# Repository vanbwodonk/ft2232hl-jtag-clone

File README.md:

# FT2232HL-jtag-clone

Digilent JTAG clone hardware + eeprom firmware (.bin). Support dual port, JTAG + Serial TTL. Hardware design using KiCad. 

## Pinout FT2232HL

JTAG:

| Pin FT2232HL | JTAG Name | FT2232 Name |
|:------------:|:---------:|:-----------:|
| 16           | TCK       | ADBUS0      |
| 17           | TDI       | ADBUS1      |
| 18           | TDO       | ADBUS2      |
| 19           | TMS       | ADBUS3      |

Serial UART:

| Pin FT2232HL | JTAG Name | FT2232 Name |
|:------------:|:---------:|:-----------:|
| 38           | TXD       | BDBUS0      |
| 39           | RXD       | BDBUS1      |

### How To Flash EEPROM

[how-to-flash](https://github.com/vanbwodonk/ft2232hl-jtag-clone/blob/main/eeprom_binary/README.md)

### Source :

Thanks to @rikka0w0 for provide binary files modification .Source : https://gist.github.com/rikka0w0/24b58b54473227502fa0334bbe75c3c1

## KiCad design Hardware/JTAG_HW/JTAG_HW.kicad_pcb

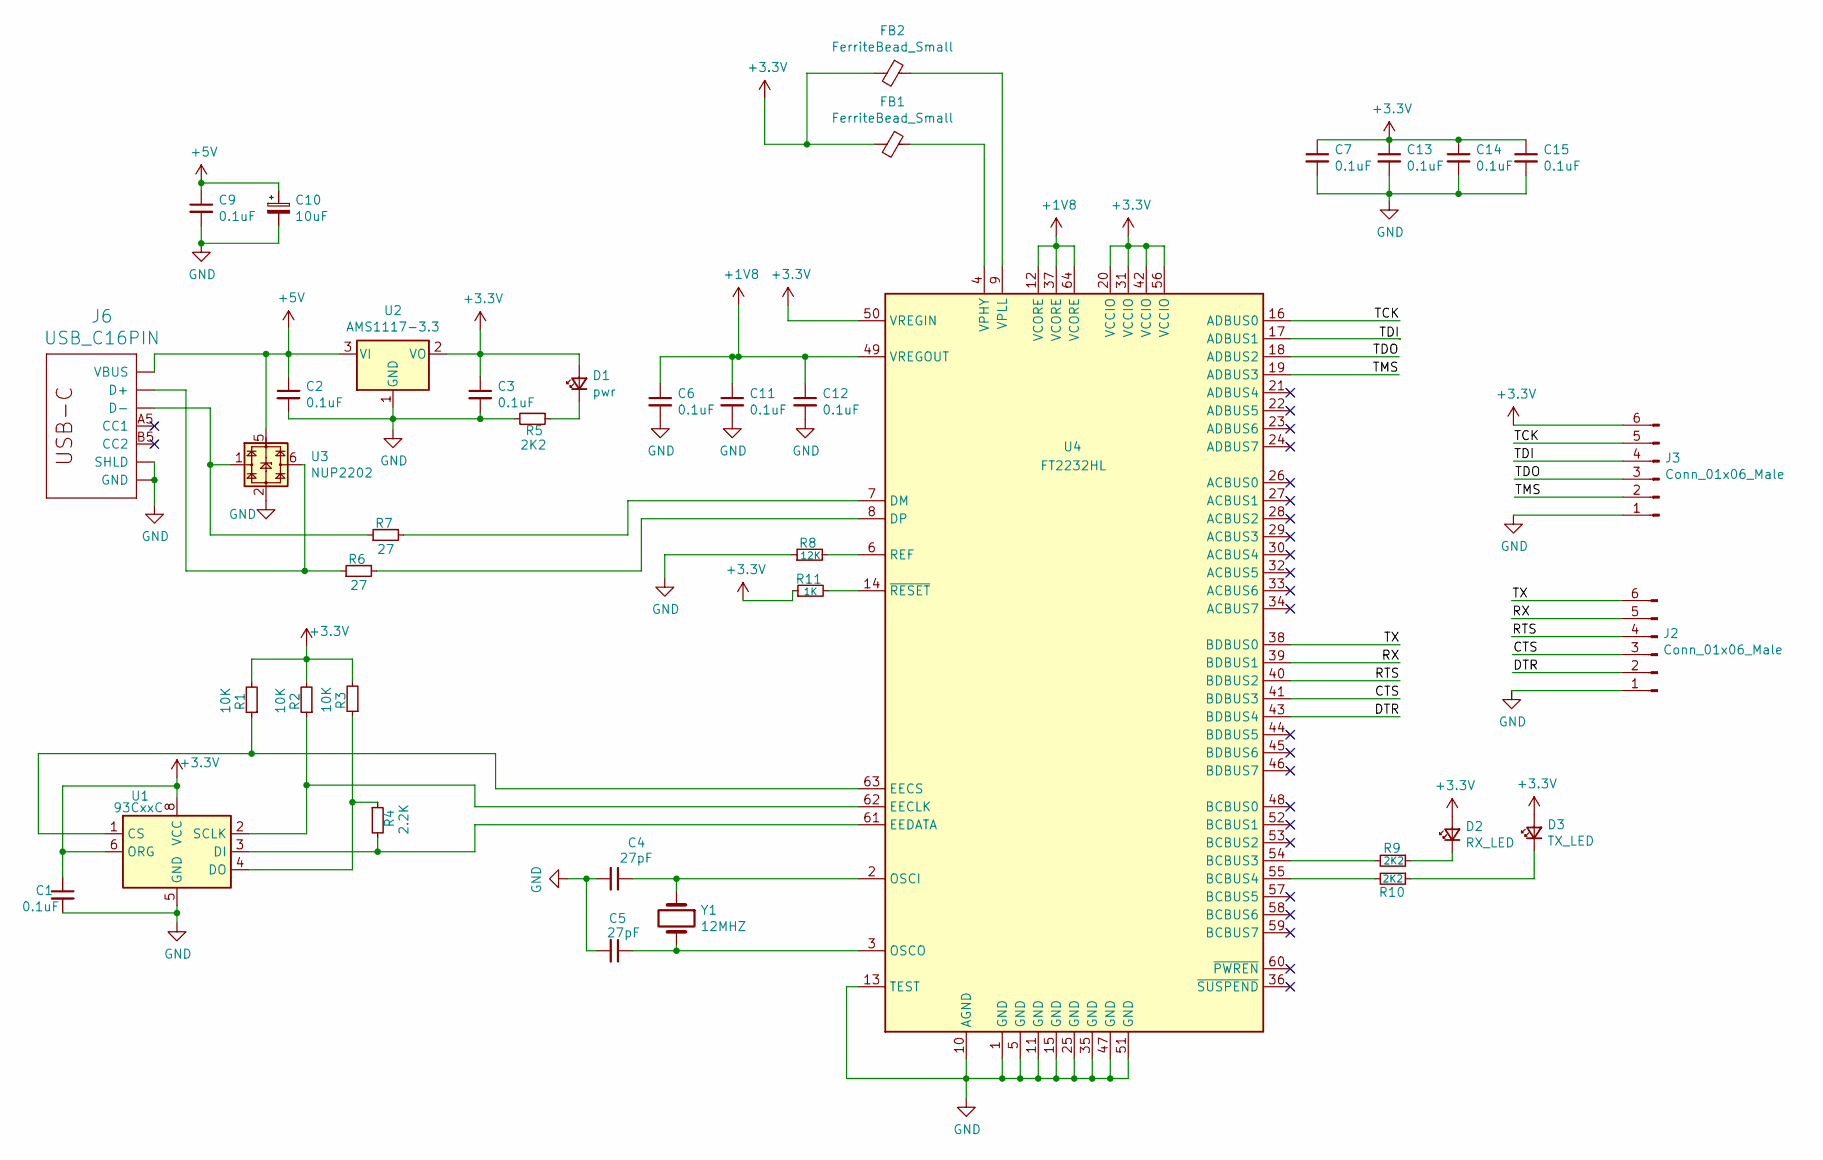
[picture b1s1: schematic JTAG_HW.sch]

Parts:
C1, C2, C3, C6, C7, C9, C11, C12, C13, C14, C15: 0.1uF; C_0805_2012Metric_Pad1.18x1.45mm_HandSolder
C4, C5: 27pF; C_0805_2012Metric_Pad1.18x1.45mm_HandSolder
C10: 10uF; CP_EIA-3216-18_Kemet-A_Pad1.58x1.35mm_HandSolder
D1: pwr; LED_0805_2012Metric_Pad1.15x1.40mm_HandSolder
D2: RX_LED; LED_0805_2012Metric_Pad1.15x1.40mm_HandSolder
D3: TX_LED; LED_0805_2012Metric_Pad1.15x1.40mm_HandSolder
FB1, FB2: FerriteBead_Small; L_0805_2012Metric_Pad1.15x1.40mm_HandSolder
J2, J3: Conn_01x06_Male; PinHeader_1x06_P2.54mm_Vertical_SMD_Pin1long
J6: USB_C16PIN; USB-C-COM-15111
R1, R2, R3: 10K; R_0805_2012Metric_Pad1.20x1.40mm_HandSolder
R4: 2.2K; R_0805_2012Metric_Pad1.20x1.40mm_HandSolder
R5, R9, R10: 2K2; R_0805_2012Metric_Pad1.20x1.40mm_HandSolder
R6, R7: 27; R_0805_2012Metric_Pad1.20x1.40mm_HandSolder
R8: 12K; R_0805_2012Metric_Pad1.20x1.40mm_HandSolder
R11: 1K; R_0805_2012Metric_Pad1.20x1.40mm_HandSolder
U1: 93CxxC; SOIC-8_3.9x4.9mm_P1.27mm
U2: AMS1117-3.3; SOT-223-3_TabPin2
U3: NUP2202; SOT-363_SC-70-6
U4: FT2232HL; LQFP-64_10x10mm_P0.5mm
Y1: 12MHZ; Crystal_SMD_0603-2Pin_6.0x3.5mm_HandSoldering

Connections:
+1V8: C6.1, C11.1, C12.1, U4.12 (VCORE), U4.37 (VCORE), U4.49 (VREGOUT), U4.64 (VCORE)
+3V3: C1.1, C3.1, C7.1, C13.1, C14.1, C15.1, D1.2 (A), D2.2 (A), D3.2 (A), FB1.2, FB2.2, J3.6, R1.2, R2.2, R3.2, R11.1, U1.6 (ORG), U1.8 (VCC), U2.2 (VO), U4.20 (VCCIO), U4.31 (VCCIO), U4.42 (VCCIO), U4.50 (VREGIN), U4.56 (VCCIO)
+5V: C2.1, C9.1, C10.1, J6.VBUS1 (VBUS), J6.VBUS2 (VBUS), U2.3 (VI), U3.5
/CTS: J2.3, U4.41 (BDBUS3)
/DTR: J2.2, U4.43 (BDBUS4)
/RTS: J2.4, U4.40 (BDBUS2)
/RX: J2.5, U4.39 (BDBUS1)
/TCK: J3.5, U4.16 (ADBUS0)
/TDI: J3.4, U4.17 (ADBUS1)
/TDO: J3.3, U4.18 (ADBUS2)
/TMS: J3.2, U4.19 (ADBUS3)
/TX: J2.6, U4.38 (BDBUS0)
GND: C1.2, C2.2, C3.2, C4.2, C5.2, C6.2, C7.2, C9.2, C10.2, C11.2, C12.2, C13.2, C14.2, C15.2, J2.1, J3.1, J6.GND, J6.GND2 (GND), J6.SHLD1 (SHLD), J6.SHLD2 (SHLD), J6.SHLD3 (SHLD), J6.SHLD4 (SHLD), J6.SHLD5 (SHLD), J6.SHLD6 (SHLD), J6.SHLD7 (SHLD), J6.SHLD8 (SHLD), R5.2, R8.1, U1.5 (GND), U2.1 (GND), U3.2, U4.1 (GND), U4.5 (GND), U4.10 (AGND), U4.11 (GND), U4.13 (TEST), U4.15 (GND), U4.25 (GND), U4.35 (GND), U4.47 (GND), U4.51 (GND)
unnamed: C4.1, U4.2 (OSCI), Y1.1
unnamed: C5.1, U4.3 (OSCO), Y1.2
unnamed: D1.1 (K), R5.1
unnamed: D2.1 (K), R9.1
unnamed: D3.1 (K), R10.1
unnamed: FB1.1, U4.4 (VPHY)
unnamed: FB2.1, U4.9 (VPLL)
unnamed: J6.A6 (D+), J6.B6 (D+), R6.1, U3.6
unnamed: J6.A7 (D-), J6.B7 (D-), R7.1, U3.1
unnamed: R1.1, U1.1 (CS), U4.63 (EECS)
unnamed: R2.1, U1.2 (SCLK), U4.62 (EECLK)
unnamed: R3.1, R4.1, U1.4 (DO)
unnamed: R4.2, U1.3 (DI), U4.61 (EEDATA)
unnamed: R6.2, U4.8 (DP)
unnamed: R7.2, U4.7 (DM)
unnamed: R8.2, U4.6 (REF)
unnamed: R9.2, U4.54 (BCBUS3)
unnamed: R10.2, U4.55 (BCBUS4)
unnamed: R11.2, U4.14 (~RESET)

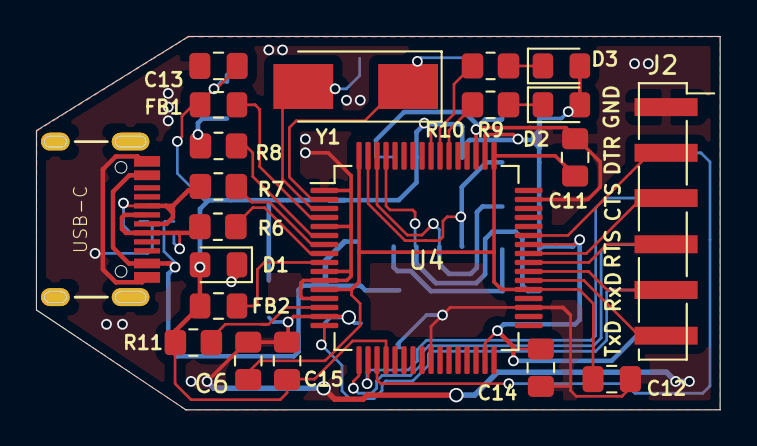
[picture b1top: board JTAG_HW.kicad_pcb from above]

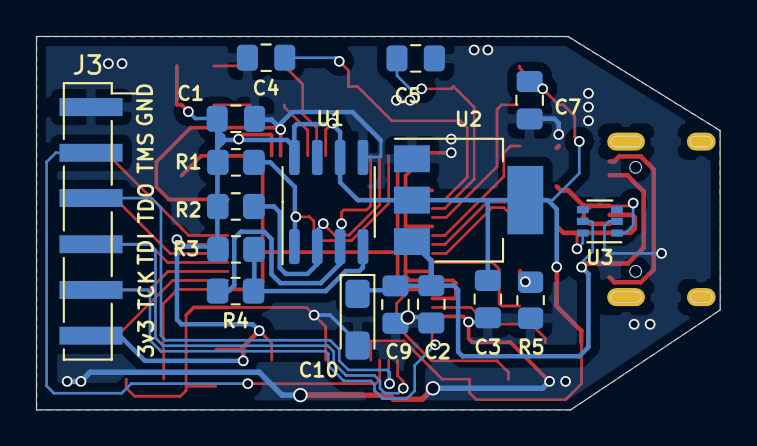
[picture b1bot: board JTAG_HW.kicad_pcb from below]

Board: 2 copper layers, 38.0 x 20.7 mm, 38 parts (17 on the bottom side), 32 nets.

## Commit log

2021-05-25 add eeprom binary
2021-05-25 add kicad files
2021-05-25 renaming folder
2022-08-18 rename origin readme
2022-08-18 Add readme how to flash
2022-08-18 add hs1 jtag
2022-08-18 rename readme.txt
